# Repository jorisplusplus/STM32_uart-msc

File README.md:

# STM32_uart-msc
STM32 uart and mass storage interface to an ESP32

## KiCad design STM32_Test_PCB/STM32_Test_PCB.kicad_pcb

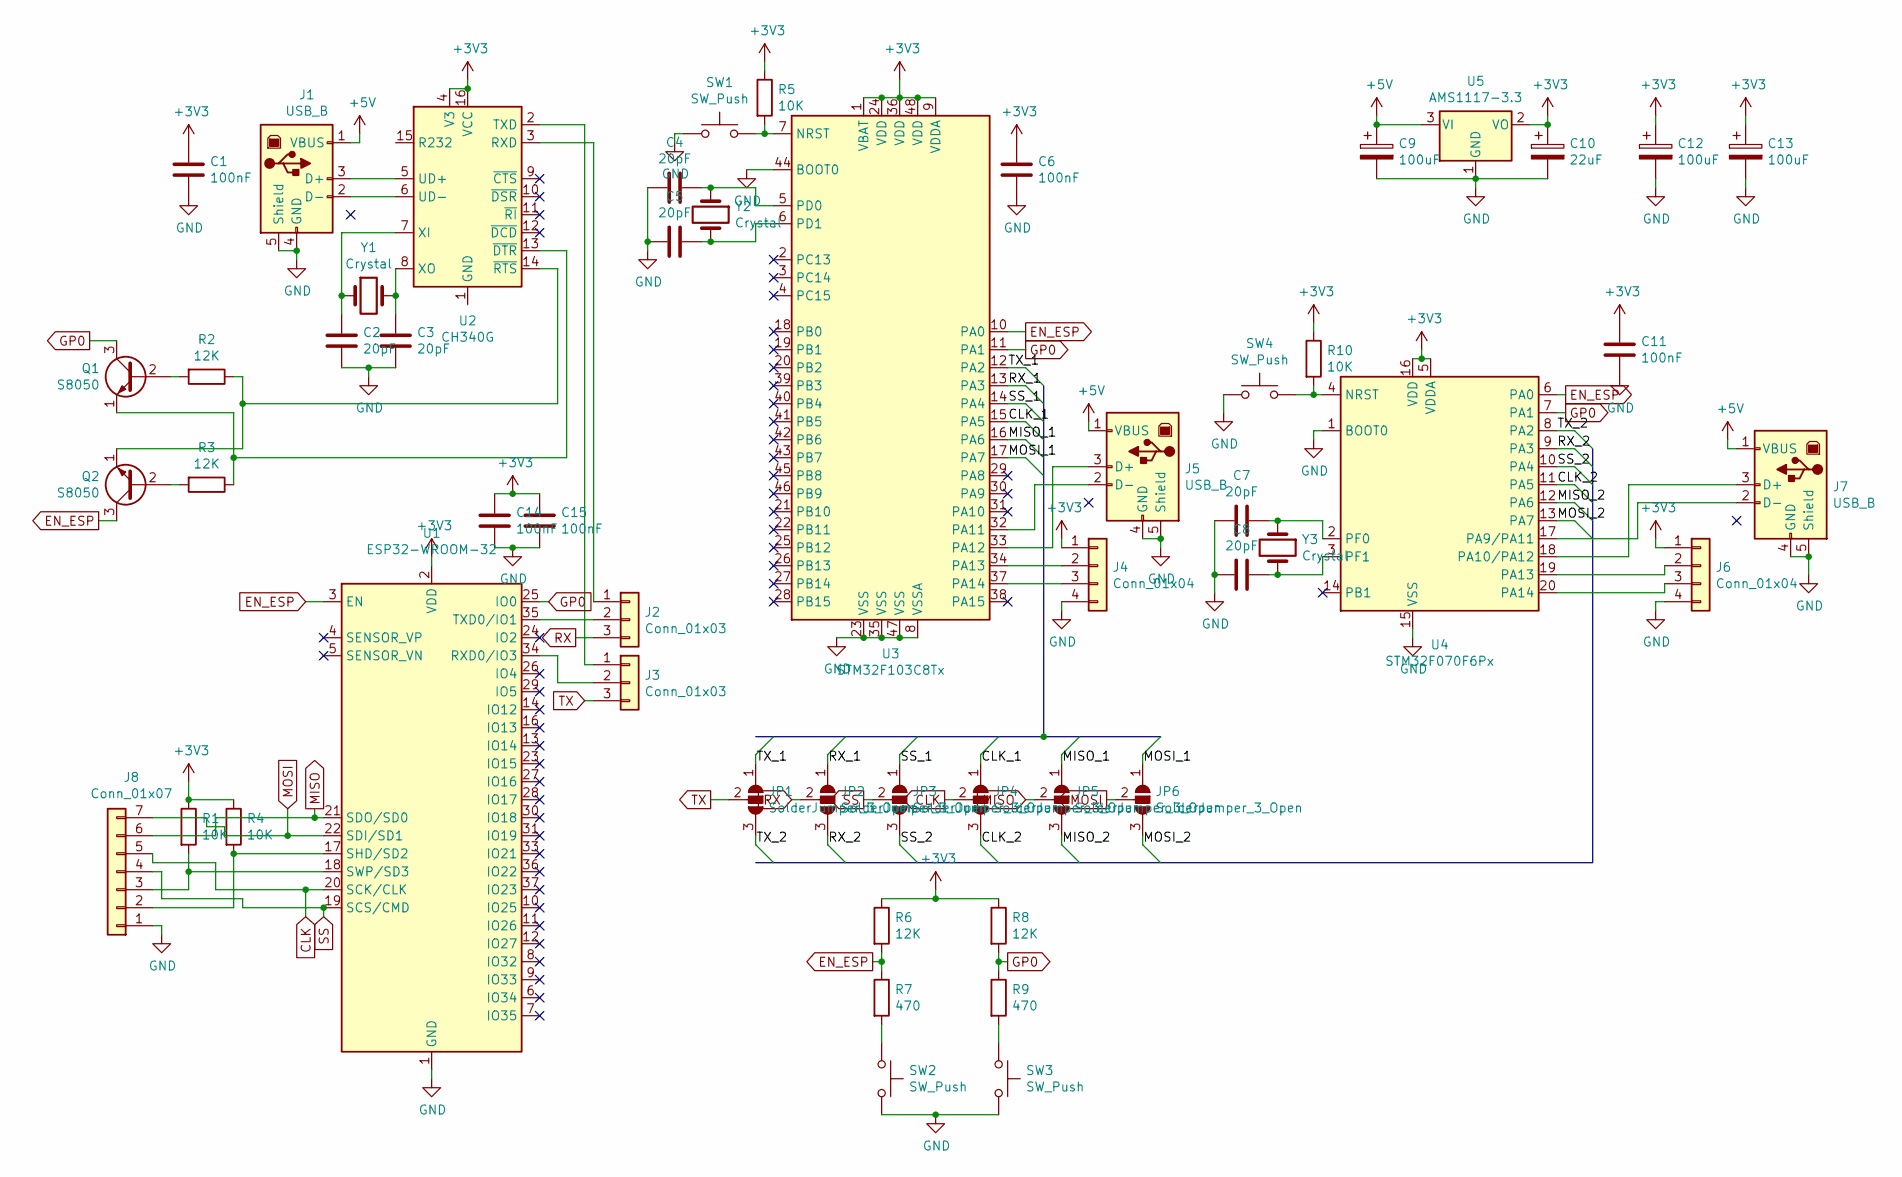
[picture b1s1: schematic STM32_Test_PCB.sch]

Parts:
C1, C6, C11, C14, C15: 100nF; C_0603_1608Metric
C2, C3, C4, C5, C7, C8: 20pF; C_0603_1608Metric
C9, C12, C13: 100uF; CP_Elec_6.3x5.4
C10: 22uF; CP_Elec_4x5.4
J1, J5, J7: USB_B; USB_B_OST_USB-B1HSxx_Horizontal
J2, J3: Conn_01x03; PinHeader_1x03_P2.54mm_Vertical
J4, J6: Conn_01x04; PinHeader_1x04_P2.54mm_Vertical
J8: Conn_01x07; PinHeader_1x07_P2.54mm_Vertical
JP1, JP2, JP3, JP4, JP5, JP6: SolderJumper_3_Open; SolderJumper-3_P1.3mm_Open_RoundedPad1.0x1.5mm
Q1, Q2: S8050; SOT-23
R1, R4, R5, R10: 10K; R_0603_1608Metric
R2, R3, R6, R8: 12K; R_0603_1608Metric
R7, R9: 470; R_0603_1608Metric
SW1, SW2, SW3, SW4: SW_Push; SW_PUSH_6mm
U1: ESP32-WROOM-32
U2: CH340G; SOIC-16_3.9x9.9mm_P1.27mm
U3: STM32F103C8Tx; LQFP-48_7x7mm_P0.5mm
U4: STM32F070F6Px; TSSOP-20_4.4x6.5mm_P0.65mm
U5: AMS1117-3.3; SOT-223-3_TabPin2
Y1, Y2, Y3: Crystal; Crystal_HC49-U_Vertical

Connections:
+3V3: C1.2, C6.2, C10.1, C11.2, C12.1, C13.1, C14.2, C15.2, J4.1, J6.1, R1.1, R4.1, R5.1, R6.1, R8.1, R10.1, U1.2 (VDD), U2.4 (V3), U2.16 (VCC), U3.1 (VBAT), U3.9 (VDDA), U3.24 (VDD), U3.36 (VDD), U3.48 (VDD), U4.5 (VDDA), U4.16 (VDD), U5.2 (VO)
+5V: C9.1, J1.1 (VBUS), J5.1 (VBUS), J7.1 (VBUS), U5.3 (VI)
/CLK_1: JP4.1 (A), U3.15 (PA5)
/CLK_2: JP4.3 (B), U4.11 (PA5)
/MISO_1: JP5.1 (A), U3.16 (PA6)
/MISO_2: JP5.3 (B), U4.12 (PA6)
/MOSI_1: JP6.1 (A), U3.17 (PA7)
/MOSI_2: JP6.3 (B), U4.13 (PA7)
/RX_1: JP2.1 (A), U3.13 (PA3)
/RX_2: JP2.3 (B), U4.9 (PA3)
/SS_1: JP3.1 (A), U3.14 (PA4)
/SS_2: JP3.3 (B), U4.10 (PA4)
/TX_1: JP1.1 (A), U3.12 (PA2)
/TX_2: JP1.3 (B), U4.8 (PA2)
CLK: J8.5, JP4.2 (C), U1.20 (SCK/CLK)
EN_ESP: Q2.3 (C), R6.2, R7.1, U1.3 (EN), U3.10 (PA0), U4.6 (PA0)
GND: C1.1, C2.1, C3.1, C4.2, C5.2, C6.1, C7.2, C8.2, C9.2, C10.2, C11.1, C12.2, C13.2, C14.1, C15.1, J1.4 (GND), J1.5 (Shield), J4.4, J5.4 (GND), J5.5 (Shield), J6.4, J7.4 (GND), J7.5 (Shield), J8.1, SW1.1, SW2.2, SW3.2, SW4.1, U1.1 (GND), U1.15 (GND), U1.38 (GND), U3.8 (VSSA), U3.23 (VSS), U3.35 (VSS), U3.44 (BOOT0), U3.47 (VSS), U4.1 (BOOT0), U4.15 (VSS), U5.1 (GND)
GP0: Q1.3 (C), R8.2, R9.1, U1.25 (IO0), U3.11 (PA1), U4.7 (PA1)
MISO: J8.6, JP5.2 (C), U1.21 (SDO/SD0)
MOSI: J8.7, JP6.2 (C), U1.22 (SDI/SD1)
unnamed: C2.2, U2.7 (XI), Y1.1
unnamed: C3.2, U2.8 (XO), Y1.2
unnamed: C4.1, U3.5 (PD0), Y2.1
unnamed: C5.1, U3.6 (PD1), Y2.2
unnamed: C7.1, U4.2 (PF0), Y3.1
unnamed: C8.1, U4.3 (PF1), Y3.2
unnamed: J1.2 (D-), U2.6 (UD-)
unnamed: J1.3 (D+), U2.5 (UD+)
unnamed: J2.1, U2.3 (RXD)
unnamed: J2.2, U1.35 (TXD0/IO1)
unnamed: J3.1, U2.2 (TXD)
unnamed: J3.2, U1.34 (RXD0/IO3)
unnamed: J4.2, U3.34 (PA13)
unnamed: J4.3, U3.37 (PA14)
unnamed: J5.2 (D-), U3.32 (PA11)
unnamed: J5.3 (D+), U3.33 (PA12)
unnamed: J6.2, U4.19 (PA13)
unnamed: J6.3, U4.20 (PA14)
unnamed: J7.2 (D-), U4.17 (PA9/PA11)
unnamed: J7.3 (D+), U4.18 (PA10/PA12)
unnamed: J8.2, R4.2, U1.17 (SHD/SD2)
unnamed: J8.3, R1.2, U1.18 (SWP/SD3)
unnamed: Q1.1 (E), R3.1, U2.13 (~DTR)
unnamed: Q1.2 (B), R2.2
unnamed: Q2.1 (E), R2.1, U2.14 (~RTS)
unnamed: Q2.2 (B), R3.2
unnamed: R5.2, SW1.2, U3.7 (NRST)
unnamed: R7.2, SW2.1
unnamed: R9.2, SW3.1
unnamed: R10.2, SW4.2, U4.4 (NRST)
RX: J2.3, JP2.2 (C)
SS: J8.4, JP3.2 (C), U1.19 (SCS/CMD)
TX: J3.3, JP1.2 (C)

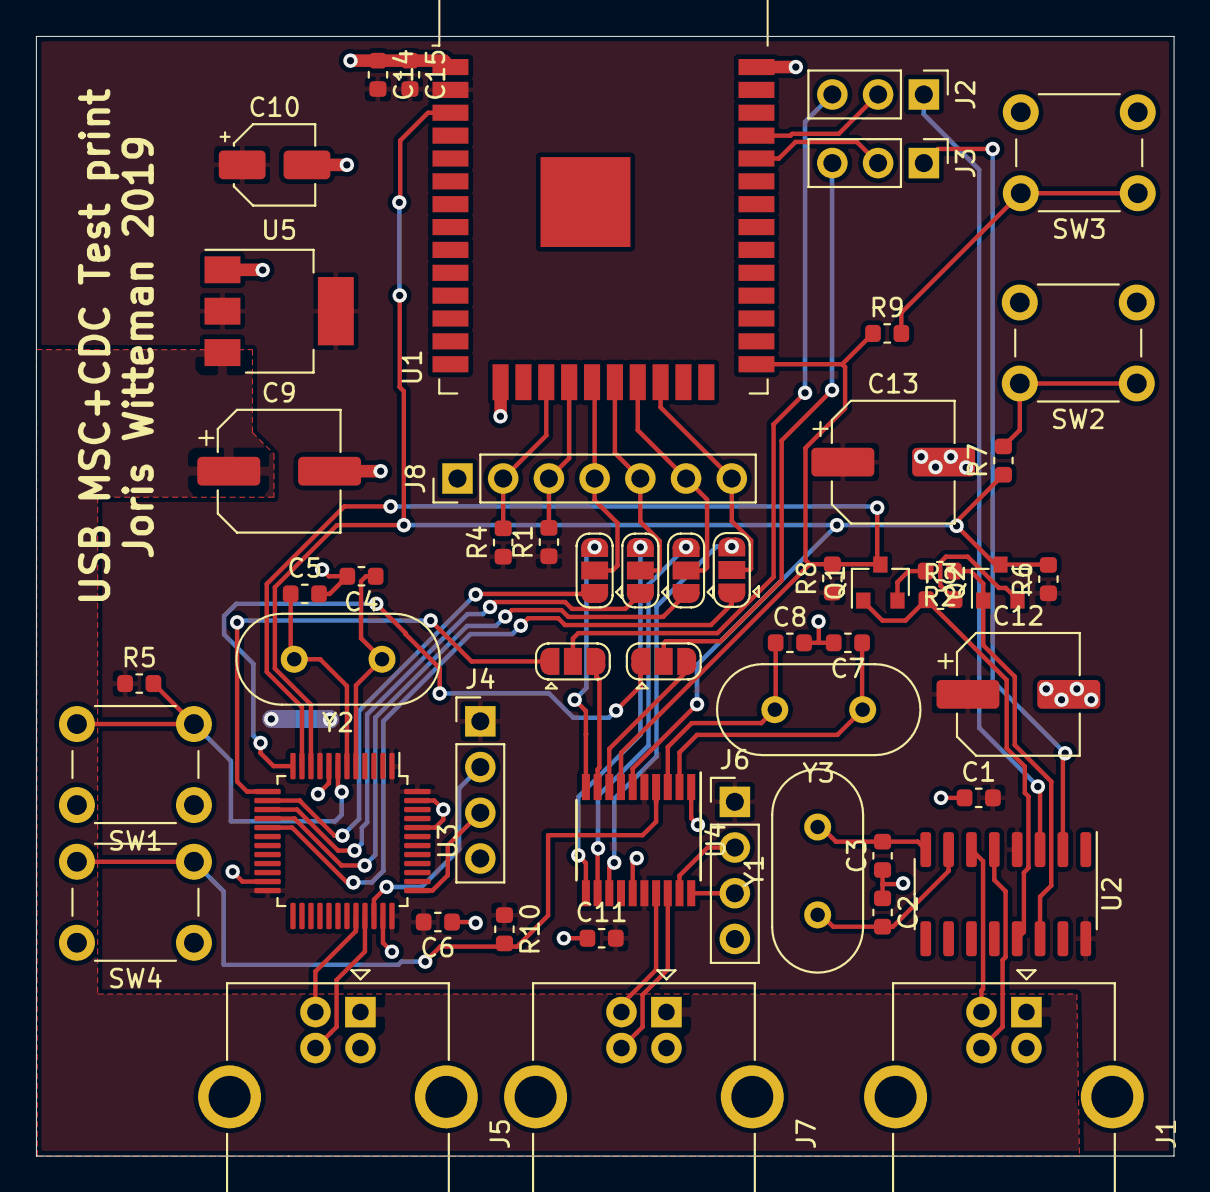
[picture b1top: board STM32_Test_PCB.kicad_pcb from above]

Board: 2 copper layers, 63.2 x 62.2 mm, 53 parts (0 on the bottom side), 53 nets.

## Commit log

2020-01-11 Added gitignore
2020-01-11 Initial CDC source
2020-01-11 Initial pcb commit
